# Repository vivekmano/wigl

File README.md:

# Wigl v0.1
An open-source robot controlled by musical notes

Based on the Arduino Uno - Atmega328P (easily compatible with other Arduino boards)

## EAGLE Schematics
Can be found under /schematics
Two versions:
Wigl v0.1 - a small board with all necessary components and 4 mount holes
Wigl V0.1-KIT - Similar to above, but circular and has cutouts for wheels, motor mount holes, etc.

## License
Wigl is available under the [MIT License](https://github.com/vivekmano/Wigl/blob/master/LICENSE.md)

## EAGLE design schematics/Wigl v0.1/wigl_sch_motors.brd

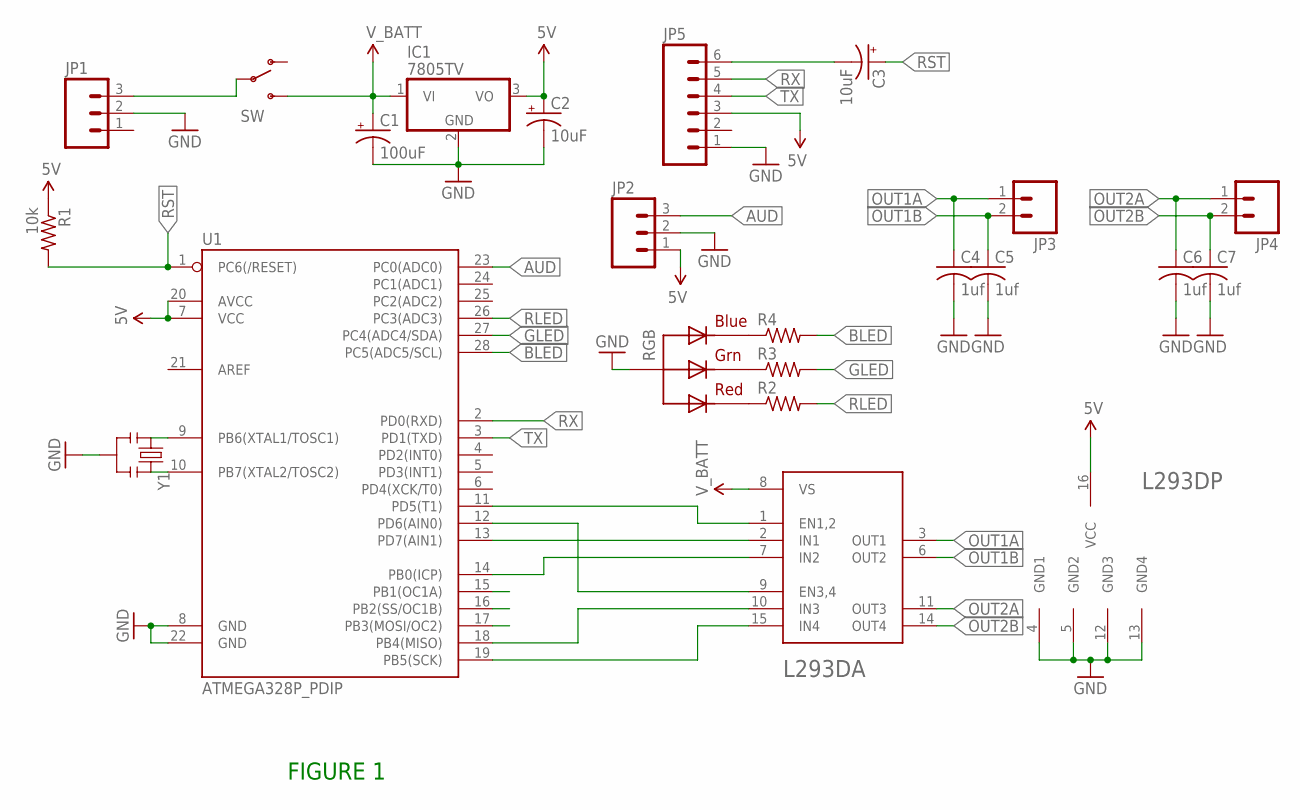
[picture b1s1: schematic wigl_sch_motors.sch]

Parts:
C1: 100uF; CPOL-RADIAL-100UF-25V
C2, C3: 10uF; CPOL-RADIAL-100UF-25V
C4, C5, C6, C7: 1uf; C025-025X050
IC1: 7805TV; TO220V
JP1, JP2: M03LONGPADS; 1X03_LONGPADS
JP3, JP4: M02LOCK_LONGPADS; 1X02_LOCK_LONGPADS
JP5: M06LONGPADS; 1X06_LONGPADS
L293D: L293D; DIP16
R1: 10k; 0204V
R2, R3, R4: R-US_0204/2V; 0204V
RGB: RGBLED_CA-5MM; LED5MMRGB
SW: SWITCH-SPDTPTH; SWITCH-SPDT
U1: ATMEGA328P_PDIP; DIL28-3
Y1: RESONATORPTH; RESONATOR-PTH

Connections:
5V: C2.1 (+), IC1.3 (VO), JP2.1, JP5.3, L293D.16 (VCC), R1.1, U1.7 (VCC), U1.20 (AVCC)
AUD: JP2.3, U1.23 (PC0(ADC0))
BLED: R4.2, U1.28 (PC5(ADC5/SCL))
GLED: R3.2, U1.27 (PC4(ADC4/SDA))
GND: C1.2 (-), C2.2 (-), C4.2, C5.2, C6.2, C7.2, IC1.2 (GND), JP1.2, JP2.2, L293D.4 (GND1), L293D.5 (GND2), L293D.12 (GND3), L293D.13 (GND4), RGB.2 (VCC), U1.8 (GND), U1.22 (GND), Y1.2
unnamed: JP1.3, SW.2
unnamed: R4.1, RGB.4 (BLUE)
unnamed: R3.1, RGB.3 (GREEN)
unnamed: C3.2 (-), JP5.6
unnamed: U1.9 (PB6(XTAL1/TOSC1)), Y1.1
unnamed: U1.10 (PB7(XTAL2/TOSC2)), Y1.3
unnamed: L293D.9 (EN3,4), U1.12 (PD6(AIN0))
unnamed: R2.1, RGB.1 (RED)
unnamed: L293D.2 (IN1), U1.13 (PD7(AIN1))
unnamed: L293D.7 (IN2), U1.14 (PB0(ICP))
unnamed: L293D.10 (IN3), U1.18 (PB4(MISO))
unnamed: L293D.15 (IN4), U1.19 (PB5(SCK))
unnamed: L293D.1 (EN1,2), U1.11 (PD5(T1))
OUT1A: C4.1, JP3.1, L293D.3 (OUT1)
OUT1B: C5.1, JP3.2, L293D.6 (OUT2)
OUT2A: C6.1, JP4.1, L293D.11 (OUT3)
OUT2B: C7.1, JP4.2, L293D.14 (OUT4)
RLED: R2.2, U1.26 (PC3(ADC3))
RST: C3.1 (+), R1.2, U1.1 (PC6(/RESET))
RX: JP5.5, U1.2 (PD0(RXD))
TX: JP5.4, U1.3 (PD1(TXD))
V_BATT: C1.1 (+), IC1.1 (VI), L293D.8 (VS), SW.3 (S)

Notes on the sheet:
FIGURE 1

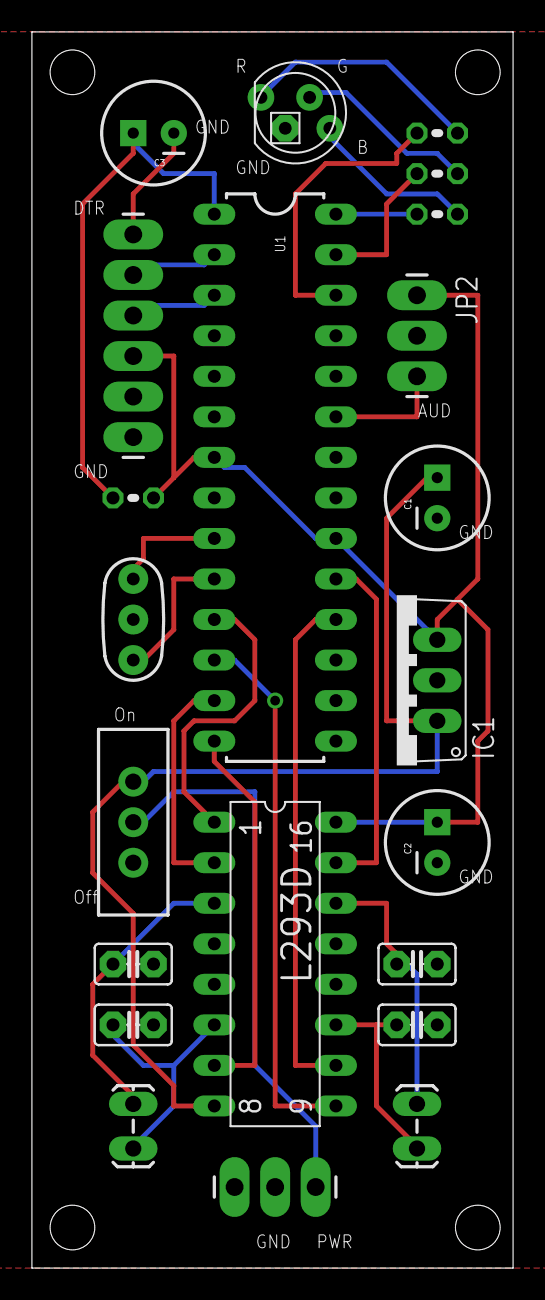
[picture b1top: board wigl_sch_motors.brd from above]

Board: 2 copper layers, 30.1 x 77.5 mm, 22 parts (0 on the bottom side), 27 nets.

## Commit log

2015-12-14 Added readme
2015-12-15 Updated LICENSE and README
2015-12-15 Updated the LICENSE
2015-12-15 Added Wigl image to README
2015-12-15 right image
2015-12-15 Added schematics
2016-02-02 Create index.html for project page
2016-02-02 Create CNAME
2016-02-02 Updated to reflect HTML5
2016-03-24 much needed website update
2016-03-24 added Google Analytics
2016-03-24 css fixes, shrinking navbar, centered open source icons
2018-10-09 fixed markdown
2021-10-28 Updated CNAME
    hopefully to fix ssl redirect issues
2021-10-29 Update CNAME
2021-10-29 bootstrap update
    Updated to v5.1
2021-10-29 updated for new ssl cert
2021-10-29 reverted back to older version
2021-11-24 trying out Transcend Consent

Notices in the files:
parts and their libraries:
SparkFun-Capacitors: Licensing: Creative Commons ShareAlike 4.0 International - https://creativecommons.org/licenses/by-sa/4.0
